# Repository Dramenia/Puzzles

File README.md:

# Puzzles
Github for puzzles in the escape room of phantom vault

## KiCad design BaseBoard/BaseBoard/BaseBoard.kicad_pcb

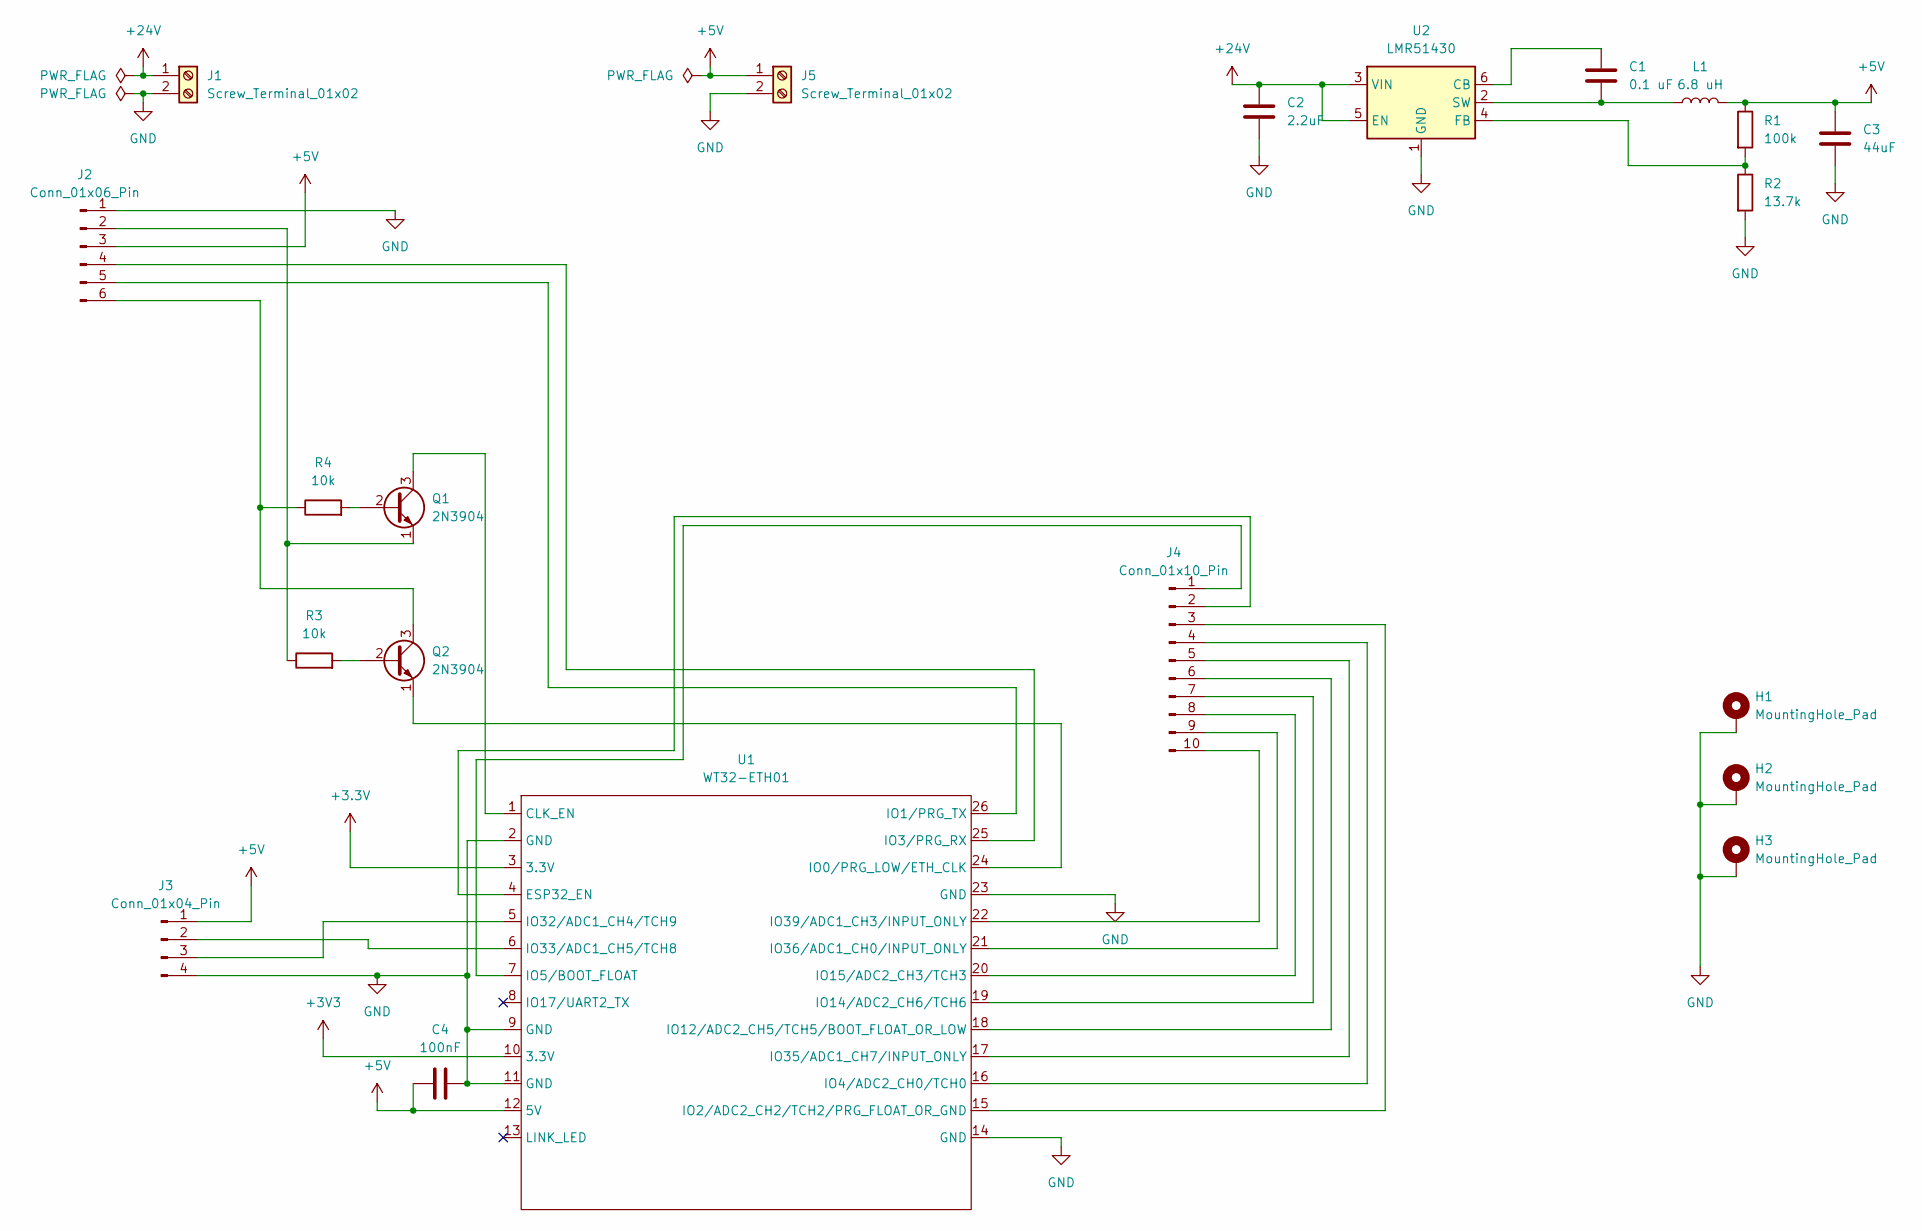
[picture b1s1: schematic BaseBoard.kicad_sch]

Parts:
C1: 0.1 uF; C_0603_1608Metric_Pad1.08x0.95mm_HandSolder
C2: 2.2uF; C_0603_1608Metric_Pad1.08x0.95mm_HandSolder
C3: 44uF; C_0603_1608Metric_Pad1.08x0.95mm_HandSolder
C4: 100nF; C_0603_1608Metric_Pad1.08x0.95mm_HandSolder
H1, H2, H3: MountingHole_Pad; MountingHole_3.2mm_M3_DIN965_Pad
J1, J5: Screw_Terminal_01x02; TerminalBlock_Phoenix_MKDS-3-2-5.08_1x02_P5.08mm_Horizontal
J2: Conn_01x06_Pin; PinHeader_1x06_P2.54mm_Vertical
J3: Conn_01x04_Pin; JST_XH_B4B-XH-A_1x04_P2.50mm_Vertical
J4: Conn_01x10_Pin; PinHeader_1x10_P2.54mm_Vertical
L1: 6.8 uH; L_Bourns_SDR0604
Q1, Q2: 2N3904; TO-92_Inline
R1: 100k; R_0603_1608Metric_Pad0.98x0.95mm_HandSolder
R2: 13.7k; R_0603_1608Metric_Pad0.98x0.95mm_HandSolder
R3, R4: 10k; R_0603_1608Metric_Pad0.98x0.95mm_HandSolder
U1: WT32-ETH01; WT32-ETH01-M
U2: LMR51430; SOT-23-6

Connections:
+3.3V: U1.3 (3.3V)
+3V3: U1.10 (3.3V)
+5V: C3.1, C4.1, J2.3, J3.1, J5.1, L1.2, R1.1, U1.12 (5V)
+24V: C2.1, J1.1, U2.3 (VIN), U2.5 (EN)
GND: C2.2, C3.2, C4.2, H1.1, H2.1, H3.1, J1.2, J2.1, J3.4, J5.2, R2.2, U1.2 (GND), U1.9 (GND), U1.11 (GND), U1.14 (GND), U1.23 (GND), U2.1 (GND)
unnamed: J2.2, Q1.1 (E), R3.1
unnamed: J2.4, U1.25 (IO3/PRG_RX)
unnamed: J2.5, U1.26 (IO1/PRG_TX)
unnamed: J2.6, Q2.3 (C), R4.1
unnamed: J3.2, U1.6 (IO33/ADC1_CH5/TCH8)
unnamed: J3.3, U1.5 (IO32/ADC1_CH4/TCH9)
unnamed: J4.1, U1.7 (IO5/BOOT_FLOAT)
unnamed: J4.2, U1.4 (ESP32_EN)
unnamed: J4.3, U1.15 (IO2/ADC2_CH2/TCH2/PRG_FLOAT_OR_GND)
unnamed: J4.4, U1.16 (IO4/ADC2_CH0/TCH0)
unnamed: J4.5, U1.17 (IO35/ADC1_CH7/INPUT_ONLY)
unnamed: J4.6, U1.18 (IO12/ADC2_CH5/TCH5/BOOT_FLOAT_OR_LOW)
unnamed: J4.7, U1.19 (IO14/ADC2_CH6/TCH6)
unnamed: J4.8, U1.20 (IO15/ADC2_CH3/TCH3)
unnamed: J4.9, U1.21 (IO36/ADC1_CH0/INPUT_ONLY)
unnamed: J4.10, U1.22 (IO39/ADC1_CH3/INPUT_ONLY)
unnamed: Q1.2 (B), R4.2
unnamed: Q1.3 (C), U1.1 (CLK_EN)
unnamed: Q2.2 (B), R3.2
unnamed: Q2.1 (E), U1.24 (IO0/PRG_LOW/ETH_CLK)
unnamed: C1.1, U2.6 (CB)
unnamed: R1.2, R2.1, U2.4 (FB)
unnamed: C1.2, L1.1, U2.2 (SW)

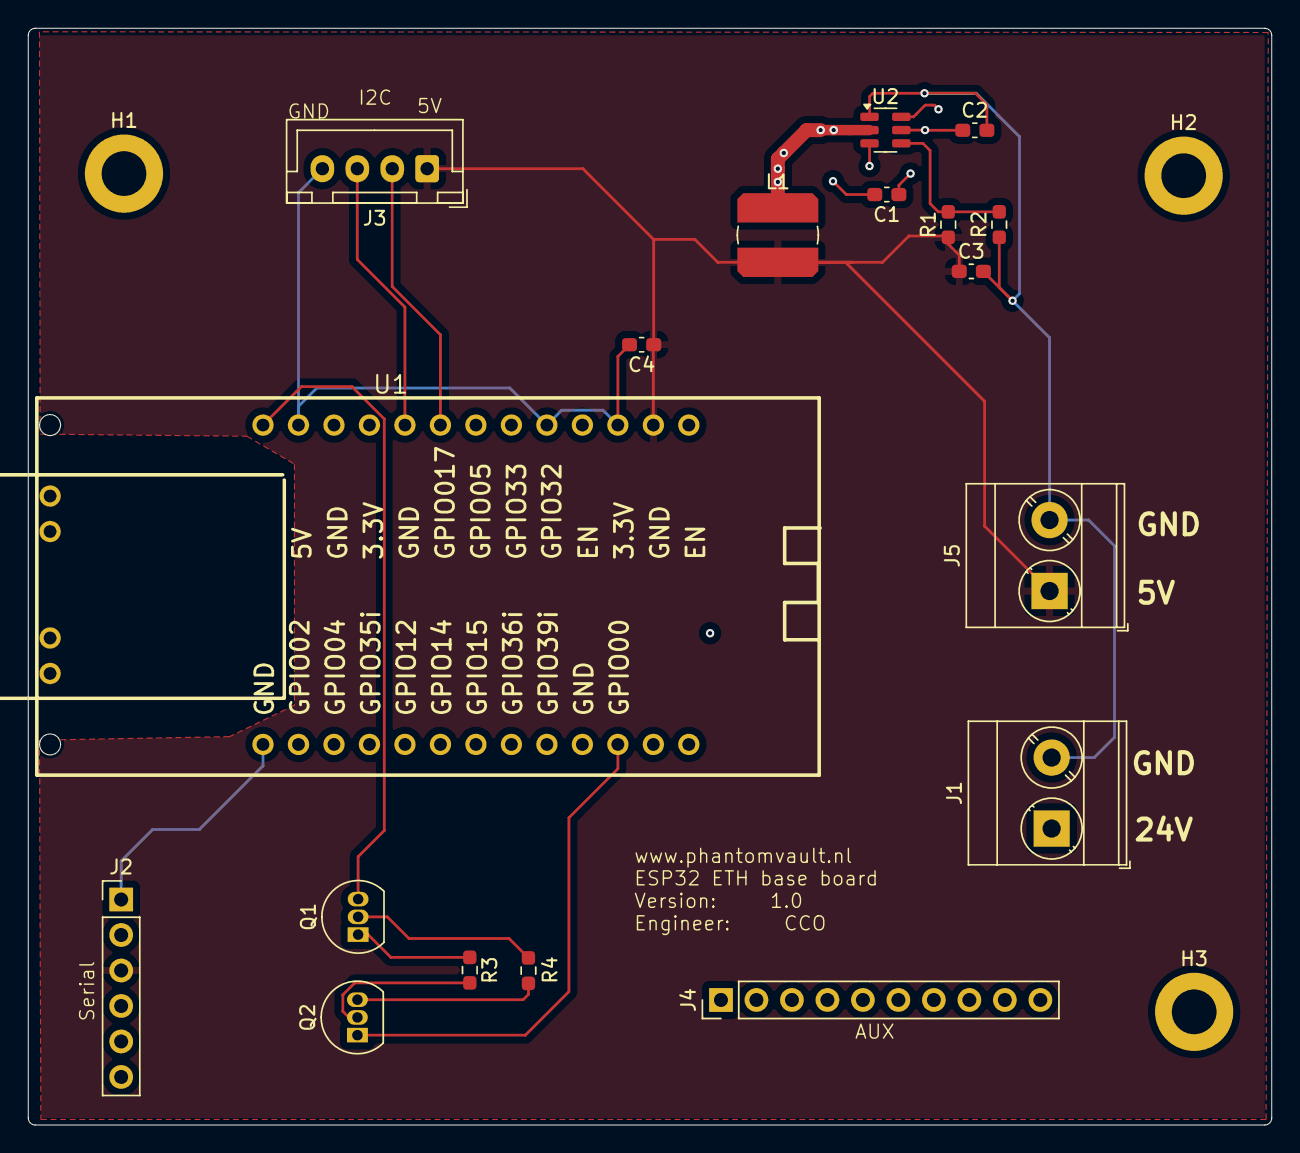
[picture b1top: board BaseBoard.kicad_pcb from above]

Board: 4 copper layers, 89.0 x 78.5 mm, 21 parts (0 on the bottom side), 26 nets.

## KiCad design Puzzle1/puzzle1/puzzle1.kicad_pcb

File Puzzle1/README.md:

# Puzzle 1:
The circuit is designed to work together with:

 - A nine-by-nine connectors grid
 - Three cables
 - Three RG LED as indicators

The goal of the circuit is detect which cable is connected to which connector. The position of the connection results in progression of the puzzle.
## The idea:
The cables are connected to three digital outputs. The digital outputs is enabled one by one. Each position of the nine by nine grid is connected to a digital input. if the digital input becomes high, the position is checked vs the currently active digital output.
In total, 81 digital inputs and 3 digital outputs are required, which is more than standard microcontrollers contain. 
## design choices
The design choices are based on the requirements and the reusability of the PCB.
### MoSCoW
The MoSCoW is based on the requirements of the current design. The MoSCoW can change during the project, since current knowledge is limited.
| Feature | MoSCoW | Description|
|--|--|--|
| 81 digital inputs | Mo | The PCB must house at least 81 digital inputs, each connected via wires |
| 3 digital outputs | Mo | The PCB must house at least 3 digital outputs |
| LED indicators	| Mo | The PCB must support at least three red and three green LEDs, each connected via wires rather than mounted directly |
| 5V usable	| Mo | The circuitry must be usable with a 5V powersupply |
| MCU independent | S | The control of the GPIO should be based on a standard bus like I2C, SPI or bit shifting |
| Ethernet connection | Co | The controls of the GPIO could be controlled via NodeRED |
| Wireless connection | Co | The GPIOs can be controlled via a wireless control, increasing the usability |

### GPIO expander
To handle the high amount of digital inputs and outputs, a GPIO expander is selected. The flexibility of the design is important. Therefor a GPIO expander is selected that can handle both 5V and 3.3V. [PCA9555](https://mou.sr/3AClXk6) from NXP was selected as an GPIO expander. The chip handles 3.3V and 5V. The GPIO expander is controlled via I2C communication, with settable addresses via 3 pins. This means that a total of 9 chips can be combined in one I2C bus. The PCA9555 has 16 configurable GPIO's. The digital outputs can deliver 50 mA per output total, and the polarity can be inversed.

### Additional
To give visual feedback, three RG LED are added to the circuit. The design now is based on 5V source. The selected RG's selected are [WP819SURKMGKW](https://mou.sr/3Chk2C6) from Kingbright. The forward voltage is 1.8 and 2.1 V typical. 30mA is typical allowed current for this LED. Therefore, 120 ohm resistors are placed on each LED.
Since the board contains parts that might break over time, interfaces are added to the board instead of the components themselves. For the connectors, nine JST connectors with nine pins are selected. For the main connection, a four pin JST connector was selected. To keep the BOM small, the same connectors are selected for the LED connections and the cable connections.
Since everything will be hand soldered, all components are selected to be ok to hand solder, like 0603 for the resistors and SO24 for the chip.

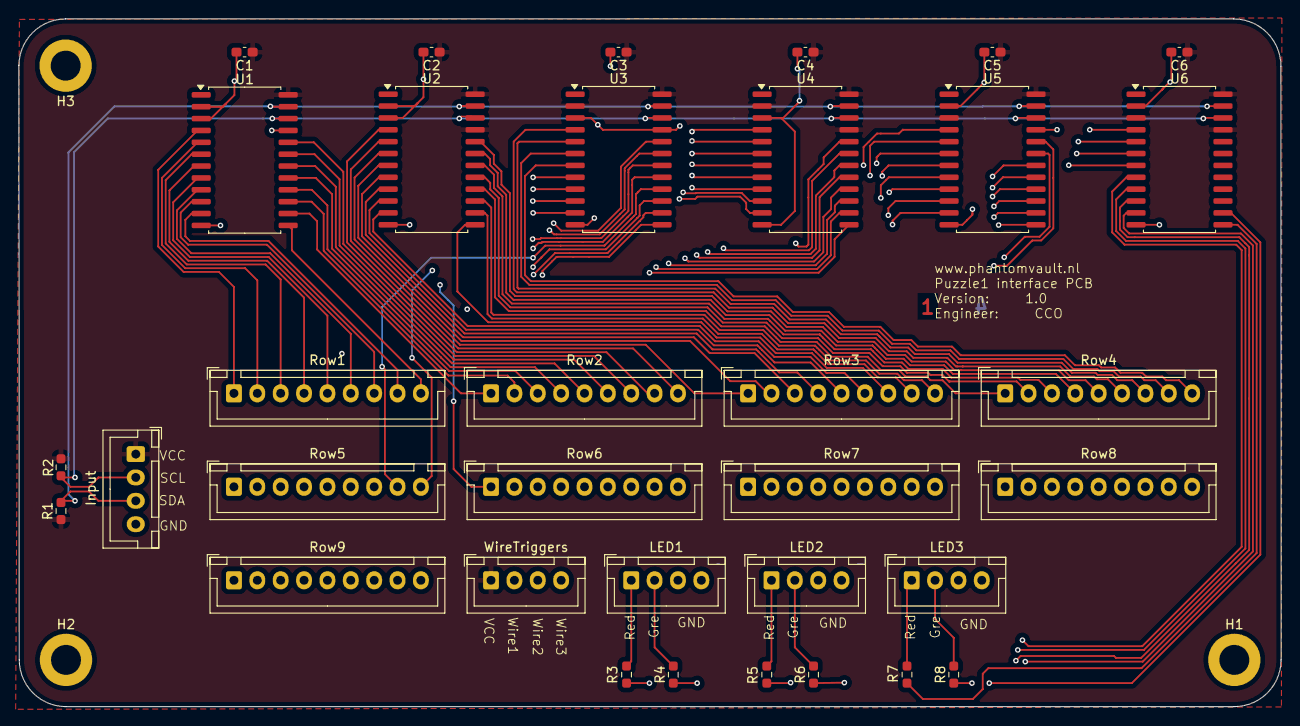
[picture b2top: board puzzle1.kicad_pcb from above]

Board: 4 copper layers, 135.0 x 73.6 mm, 37 parts (0 on the bottom side), 100 nets.

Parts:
C1, C2, C3, C4, C5, C6: 100n; C_0603_1608Metric_Pad1.08x0.95mm_HandSolder
H1, H2, H3: MountingHole_Pad; MountingHole_3.2mm_M3_DIN965_Pad
Input: Conn_01x04_Pin; JST_XH_B4B-XH-A_1x04_P2.50mm_Vertical
LED1, LED2, LED3: Conn_01x04_Pin; JST_XH_B4B-XH-A_1x04_P2.50mm_Vertical
R1, R2: 4.7k; R_0603_1608Metric_Pad0.98x0.95mm_HandSolder
R3, R4, R5, R6, R7, R8: 120; R_0603_1608Metric_Pad0.98x0.95mm_HandSolder
Row1, Row2, Row3, Row4, Row5, Row6, Row7, Row8, Row9: Conn_01x09_Pin; JST_XH_B9B-XH-A_1x09_P2.50mm_Vertical
U1, U2, U3, U4, U5, U6: PCA9555D; SOIC-24W_7.5x15.4mm_P1.27mm
WireTriggers: Conn_01x04_Pin; JST_XH_B4B-XH-A_1x04_P2.50mm_Vertical

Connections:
/Connectors/GPIO_1: Row1.1, U1.4 (IO0_0)
/Connectors/GPIO_2: Row1.2, U1.5 (IO0_1)
/Connectors/GPIO_3: Row1.3, U1.6 (IO0_2)
/Connectors/GPIO_4: Row1.4, U1.7 (IO0_3)
/Connectors/GPIO_5: Row1.5, U1.8 (IO0_4)
/Connectors/GPIO_6: Row1.6, U1.9 (IO0_5)
/Connectors/GPIO_7: Row1.7, U1.10 (IO0_6)
/Connectors/GPIO_8: Row1.8, U1.11 (IO0_7)
/Connectors/GPIO_9: Row1.9, U1.13 (IO1_0)
/Connectors/GPIO_10: Row2.1, U1.14 (IO1_1)
/Connectors/GPIO_11: Row2.2, U1.15 (IO1_2)
/Connectors/GPIO_12: Row2.3, U1.16 (IO1_3)
/Connectors/GPIO_13: Row2.4, U1.17 (IO1_4)
/Connectors/GPIO_14: Row2.5, U1.18 (IO1_5)
/Connectors/GPIO_15: Row2.6, U1.19 (IO1_6)
/Connectors/GPIO_16: Row2.7, U1.20 (IO1_7)
/Connectors/GPIO_17: Row2.8, U2.4 (IO0_0)
/Connectors/GPIO_18: Row2.9, U2.5 (IO0_1)
/Connectors/GPIO_19: Row3.1, U2.6 (IO0_2)
/Connectors/GPIO_20: Row3.2, U2.7 (IO0_3)
/Connectors/GPIO_21: Row3.3, U2.8 (IO0_4)
/Connectors/GPIO_22: Row3.4, U2.9 (IO0_5)
/Connectors/GPIO_23: Row3.5, U2.10 (IO0_6)
/Connectors/GPIO_24: Row3.6, U2.11 (IO0_7)
/Connectors/GPIO_25: Row3.7, U2.13 (IO1_0)
/Connectors/GPIO_26: Row3.8, U2.14 (IO1_1)
/Connectors/GPIO_27: Row3.9, U2.15 (IO1_2)
/Connectors/GPIO_28: Row4.1, U2.16 (IO1_3)
/Connectors/GPIO_29: Row4.2, U2.17 (IO1_4)
/Connectors/GPIO_30: Row4.3, U2.18 (IO1_5)
/Connectors/GPIO_31: Row4.4, U2.19 (IO1_6)
/Connectors/GPIO_32: Row4.5, U2.20 (IO1_7)
/Connectors/GPIO_33: Row4.6, U3.4 (IO0_0)
/Connectors/GPIO_34: Row4.7, U3.5 (IO0_1)
/Connectors/GPIO_35: Row4.8, U3.6 (IO0_2)
/Connectors/GPIO_36: Row4.9, U3.7 (IO0_3)
/Connectors/GPIO_37: Row5.1, U3.8 (IO0_4)
/Connectors/GPIO_38: Row5.2, U3.9 (IO0_5)
/Connectors/GPIO_39: Row5.3, U3.10 (IO0_6)
/Connectors/GPIO_40: Row5.4, U3.11 (IO0_7)
/Connectors/GPIO_41: Row5.5, U3.13 (IO1_0)
/Connectors/GPIO_42: Row5.6, U3.14 (IO1_1)
/Connectors/GPIO_43: Row5.7, U3.15 (IO1_2)
/Connectors/GPIO_44: Row5.8, U3.16 (IO1_3)
/Connectors/GPIO_45: Row5.9, U3.17 (IO1_4)
/Connectors/GPIO_46: Row6.1, U3.18 (IO1_5)
/Connectors/GPIO_47: Row6.2, U3.19 (IO1_6)
/Connectors/GPIO_48: Row6.3, U3.20 (IO1_7)
/Connectors/GPIO_49: Row6.4, U4.4 (IO0_0)
/Connectors/GPIO_50: Row6.5, U4.5 (IO0_1)
/Connectors/GPIO_51: Row6.6, U4.6 (IO0_2)
/Connectors/GPIO_52: Row6.7, U4.7 (IO0_3)
/Connectors/GPIO_53: Row6.8, U4.8 (IO0_4)
/Connectors/GPIO_54: Row6.9, U4.9 (IO0_5)
/Connectors/GPIO_55: Row7.1, U4.10 (IO0_6)
/Connectors/GPIO_56: Row7.2, U4.11 (IO0_7)
/Connectors/GPIO_57: Row7.3, U4.13 (IO1_0)
/Connectors/GPIO_58: Row7.4, U4.14 (IO1_1)
/Connectors/GPIO_59: Row7.5, U4.15 (IO1_2)
/Connectors/GPIO_60: Row7.6, U4.16 (IO1_3)
/Connectors/GPIO_61: Row7.7, U4.17 (IO1_4)
/Connectors/GPIO_62: Row7.8, U4.18 (IO1_5)
/Connectors/GPIO_63: Row7.9, U4.19 (IO1_6)
/Connectors/GPIO_64: Row8.1, U4.20 (IO1_7)
/Connectors/GPIO_65: Row8.2, U5.4 (IO0_0)
/Connectors/GPIO_66: Row8.3, U5.5 (IO0_1)
/Connectors/GPIO_67: Row8.4, U5.6 (IO0_2)
/Connectors/GPIO_68: Row8.5, U5.7 (IO0_3)
/Connectors/GPIO_69: Row8.6, U5.8 (IO0_4)
/Connectors/GPIO_70: Row8.7, U5.9 (IO0_5)
/Connectors/GPIO_71: Row8.8, U5.10 (IO0_6)
/Connectors/GPIO_72: Row8.9, U5.11 (IO0_7)
/Connectors/GPIO_73: Row9.1, U5.13 (IO1_0)
/Connectors/GPIO_74: Row9.2, U5.14 (IO1_1)
/Connectors/GPIO_75: Row9.3, U5.15 (IO1_2)
/Connectors/GPIO_76: Row9.4, U5.16 (IO1_3)
/Connectors/GPIO_77: Row9.5, U5.17 (IO1_4)
/Connectors/GPIO_78: Row9.6, U5.18 (IO1_5)
/Connectors/GPIO_79: Row9.7, U5.19 (IO1_6)
/Connectors/GPIO_80: Row9.8, U5.20 (IO1_7)
/Connectors/GPIO_81: Row9.9, U6.4 (IO0_0)
/Connectors/GPIO_82: U6.5 (IO0_1), WireTriggers.2
/Connectors/GPIO_83: U6.6 (IO0_2), WireTriggers.3
/Connectors/GPIO_84: U6.7 (IO0_3), WireTriggers.4
/Connectors/GPIO_85: R3.2, U6.8 (IO0_4)
/Connectors/GPIO_86: R4.1, U6.9 (IO0_5)
/Connectors/GPIO_87: R5.2, U6.10 (IO0_6)
/Connectors/GPIO_88: R6.1, U6.11 (IO0_7)
/Connectors/GPIO_89: R7.2, U6.13 (IO1_0)
/Connectors/GPIO_90: R8.1, U6.14 (IO1_1)
/SCL: Input.2, R2.2, U1.22 (SCL), U2.22 (SCL), U3.22 (SCL), U4.22 (SCL), U5.22 (SCL), U6.22 (SCL)
/SDA: Input.3, R1.2, U1.23 (SDA), U2.23 (SDA), U3.23 (SDA), U4.23 (SDA), U5.23 (SDA), U6.23 (SDA)
GND: C1.2, C2.2, C3.2, C4.2, C5.2, C6.2, H1.1, H2.1, H3.1, Input.4, LED1.3, LED1.4, LED2.3, LED2.4, LED3.3, LED3.4, U1.2 (A1), U1.3 (A2), U1.12 (VSS), U1.21 (A0), U2.2 (A1), U2.3 (A2), U2.12 (VSS), U3.3 (A2), U3.12 (VSS), U3.21 (A0), U4.3 (A2), U4.12 (VSS), U5.2 (A1), U5.12 (VSS), U5.21 (A0), U6.2 (A1), U6.12 (VSS)
unnamed: LED1.1, R3.1
unnamed: LED1.2, R4.2
unnamed: LED2.1, R5.1
unnamed: LED2.2, R6.2
unnamed: LED3.1, R7.1
unnamed: LED3.2, R8.2
VCC: C1.1, C2.1, C3.1, C4.1, C5.1, C6.1, Input.1, R1.1, R2.1, U1.24 (VDD), U2.21 (A0), U2.24 (VDD), U3.2 (A1), U3.24 (VDD), U4.2 (A1), U4.21 (A0), U4.24 (VDD), U5.3 (A2), U5.24 (VDD), U6.3 (A2), U6.21 (A0), U6.24 (VDD), WireTriggers.1

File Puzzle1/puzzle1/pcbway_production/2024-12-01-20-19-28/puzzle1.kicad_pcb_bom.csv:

Designator,Quantity,Value,Footprint,Package,MPN,DNP,Mount_Type,Description
"C1, C2, C3, C4, C5, C6",6,100n,C_0603_1608Metric_Pad1.08x0.95mm_HandSolder,,,,smt,Unpolarized capacitor
"Input, LED1, LED2, LED3, WireTriggers",5,Conn_01x04_Pin,JST_XH_B4B-XH-A_1x04_P2.50mm_Vertical,,,,tht,"Generic connector, single row, 01x04, script generated"
"R1, R2",2,4.7k,R_0603_1608Metric_Pad0.98x0.95mm_HandSolder,,,,smt,Resistor
"R3, R4, R5, R6, R7, R8",6,120,R_0603_1608Metric_Pad0.98x0.95mm_HandSolder,,,,smt,Resistor
"Row1, Row2, Row3, Row4, Row5, Row6, Row7, Row8, Row9",9,Conn_01x09_Pin,JST_XH_B9B-XH-A_1x09_P2.50mm_Vertical,,,,tht,"Generic connector, single row, 01x09, script generated"
"U1, U2, U3, U4, U5, U6",6,PCA9555D,SOIC-24W_7.5x15.4mm_P1.27mm,,,,smt,"IO expander 16 GPIO, I2C 400kHz, Interrupt, 2.3 - 5.5V, SOIC-24"

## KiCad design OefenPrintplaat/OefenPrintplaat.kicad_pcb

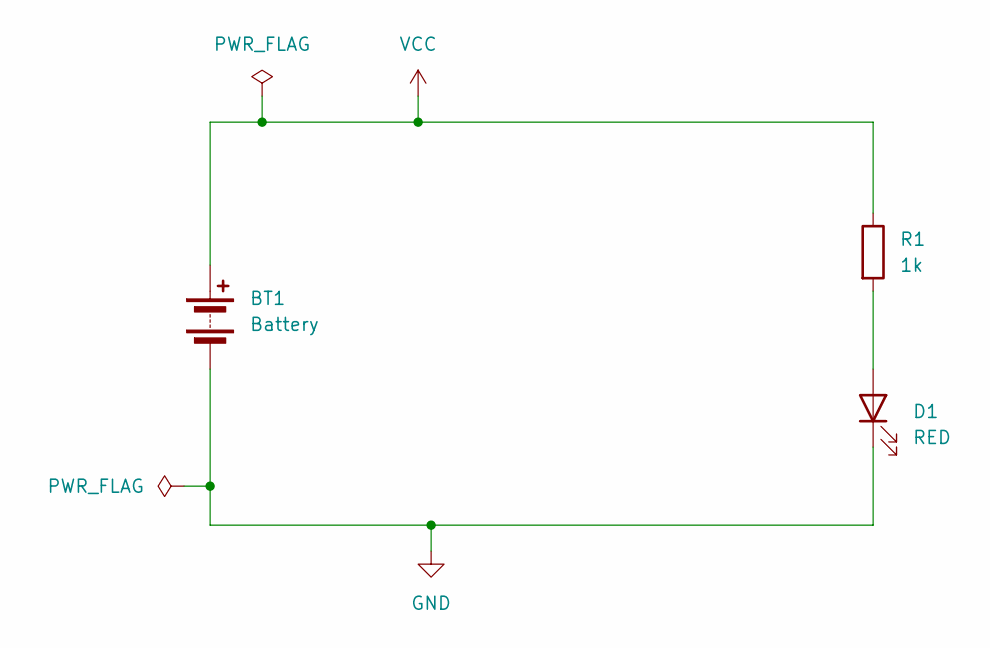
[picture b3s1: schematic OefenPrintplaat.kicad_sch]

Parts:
BT1: Battery; Battery_Panasonic_CR1025-VSK_Vertical_CircularHoles
D1: RED; LED_0603_1608Metric
R1: 1k; R_0603_1608Metric

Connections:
GND: BT1.2 (-), D1.1 (K)
unnamed: D1.2 (A), R1.2
VCC: BT1.1 (+), R1.1

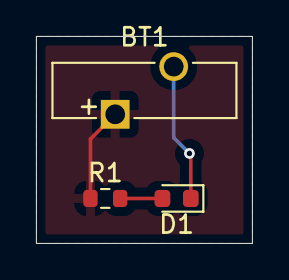
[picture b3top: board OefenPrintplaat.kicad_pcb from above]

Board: 2 copper layers, 12.0 x 11.5 mm, 3 parts (0 on the bottom side), 3 nets.

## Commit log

2024-10-29 initial push puzzle 1
2024-10-31 small update, nothing defined
2024-11-01 update oefenprintplaat
2024-11-06 update
    working on PCB layout
2024-11-08 pre-check
2024-11-09 added readme
2024-11-24 update
    not finished, but working with the busses now
2024-11-28 update after review
2025-02-02 added base board to designs, not fully done yet
    weekend update
2025-03-10 zitten fout in
    zitten fout in, niet gebruiken
